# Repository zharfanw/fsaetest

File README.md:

# UII's FSAE Car TEST

<!--stackedit_data:
eyJoaXN0b3J5IjpbNDYwMDQ0OTMzXX0=
-->

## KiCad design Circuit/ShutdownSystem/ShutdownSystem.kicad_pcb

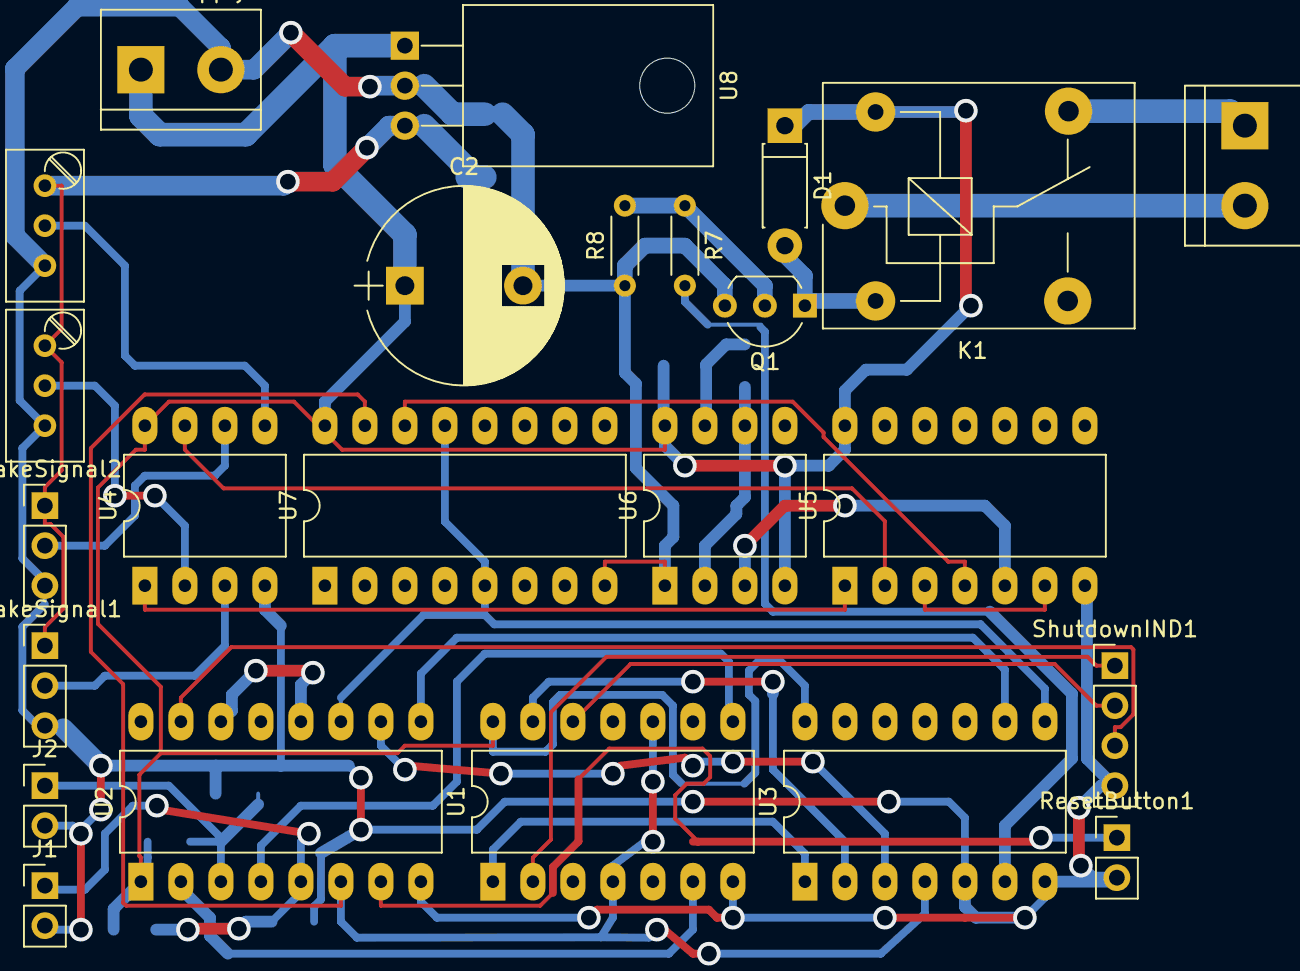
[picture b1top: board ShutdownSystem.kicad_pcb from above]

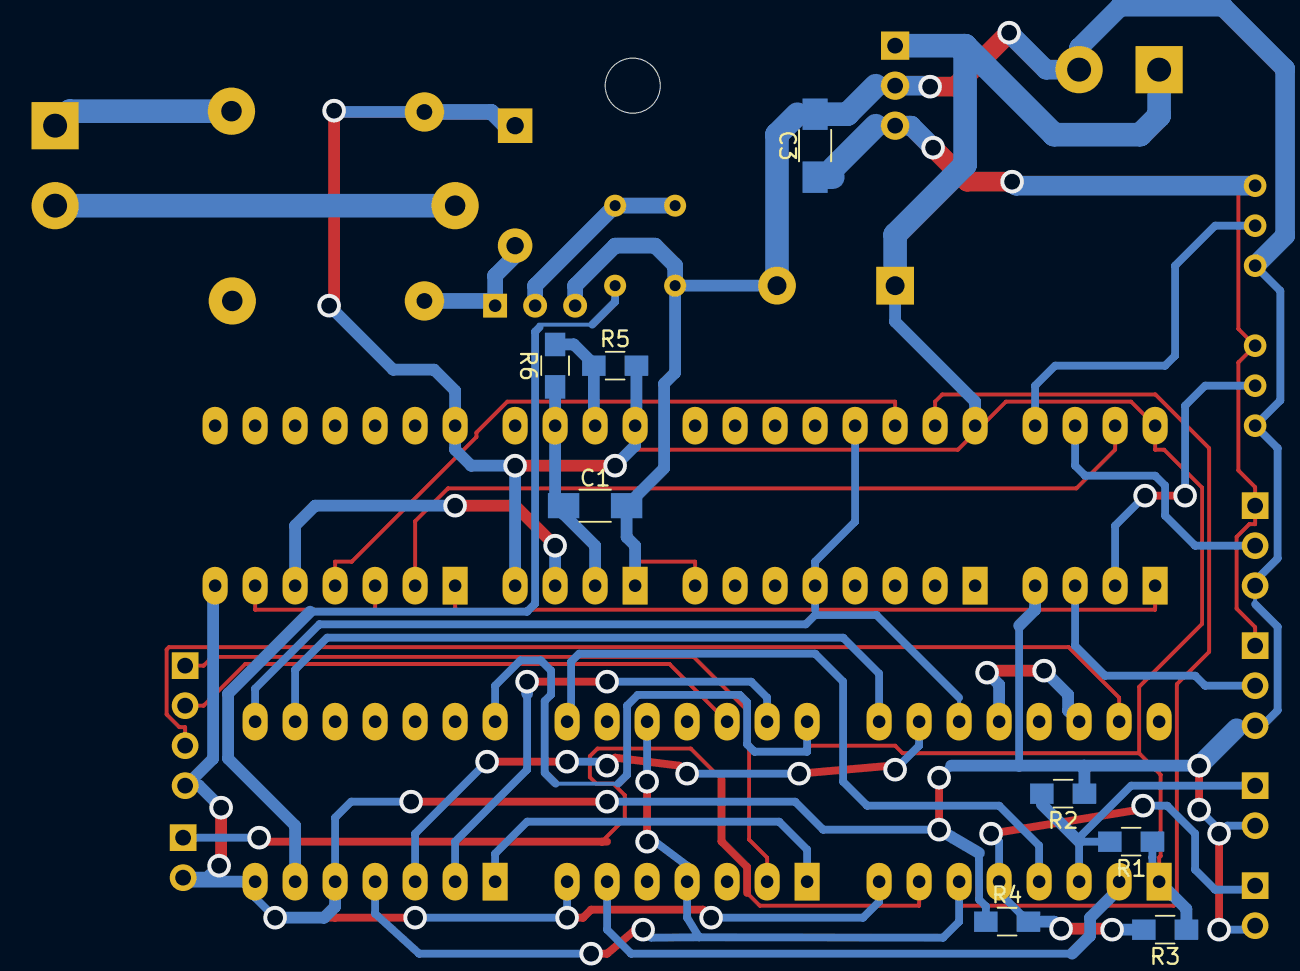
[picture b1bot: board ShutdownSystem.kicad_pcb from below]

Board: 2 copper layers, 32 parts (8 on the bottom side), 34 nets.

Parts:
BrakeSignal1, BrakeSignal2: XH_3p; Pin_Header_Straight_1x03_Pitch2.54mm
C1: 4u7F; C_1206_HandSoldering
C2: 100uF; CP_Radial_D12.5mm_P7.50mm
C3: 10uF; C_1206_HandSoldering
D1: D; D_DO-41_SOD81_P7.62mm_Horizontal
J1, J2: Conn_01x02_Male; Pin_Header_Straight_1x02_Pitch2.54mm
K1: SANYOU_SRD_Form_C; Relay_SPDT_SANYOU_SRD_Series_Form_C
PowerSupply1: TerminalBlock_2p; TerminalBlock_bornier-2_P5.08mm
Q1: 2N3906; TO-92_Inline_Wide
R1, R2, R3, R4: R; R_0805_HandSoldering
R5: 3k; R_0805_HandSoldering
R6: 13k; R_0805_HandSoldering
R7, R8: R; R_Axial_DIN0204_L3.6mm_D1.6mm_P5.08mm_Horizontal
RV1, RV2: 10k; Potentiometer_Trimmer_Bourns_3296W
ResetButton1: Xh_2p; Pin_Header_Straight_1x02_Pitch2.54mm
ShutdownCircuit1: TerminalBlock_2p; TerminalBlock_bornier-2_P5.08mm
ShutdownIND1: Conn_01x04; Pin_Header_Straight_1x04_Pitch2.54mm
U1: 4013; DIP-14_W10.16mm_LongPads
U2: 4049; DIP-16_W10.16mm_LongPads
U3: 4025; DIP-14_W10.16mm_LongPads
U4: TL072; DIP-8_W10.16mm_LongPads
U5: 4081; DIP-14_W10.16mm_LongPads
U6: NE555; DIP-8_W10.16mm_LongPads
U7: 4017; DIP-16_W10.16mm_LongPads
U8: L7805; TO-220-3_Horizontal

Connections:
+5V: BrakeSignal1.1, BrakeSignal2.1, C3.1, RV1.1, RV2.1, U8.3
/BMS_IND: ShutdownIND1.1, U1.2
/BMS_Status: J2.1, R1.2, R2.2, U2.3
/BSPD_Status: U2.11, U3.8, U7.5, U7.13
/Clock: U5.5, U6.3
/IMD_IND: ShutdownIND1.2, U1.12
/IMD_Status: J1.1, R3.2, R4.2, U2.5
/Reset: ResetButton1.1, U2.7
/Shutdown_IN: K1.4, ShutdownCircuit1.1
/Shutdown_OUT: K1.1, ShutdownCircuit1.2
GND: BrakeSignal1.3, BrakeSignal2.3, C1.2, C2.2, C3.2, J1.2, J2.2, PowerSupply1.2, Q1.3, R2.1, R4.1, R8.1, RV1.3, RV2.3, ResetButton1.2, ShutdownIND1.4, U1.7, U2.8, U3.5, U3.7, U4.4, U5.7, U6.1, U7.8, U8.2
unnamed: BrakeSignal1.2, U4.3
unnamed: BrakeSignal2.2, U4.6
unnamed: C1.1, R6.1, U6.2, U6.6
unnamed: D1.2, K1.2, Q1.1
unnamed: Q1.2, R7.1, R8.2
unnamed: R5.1, R6.2, U6.7
unnamed: R7.2, U3.6
unnamed: RV1.2, U4.2
unnamed: RV2.2, U4.5
unnamed: ShutdownIND1.3, U2.15
unnamed: U1.1, U3.1
unnamed: U1.6, U2.2
unnamed: U1.8, U2.4
unnamed: U1.4, U1.10, U2.6, U3.4, U7.15
unnamed: U1.13, U3.2
unnamed: U2.9, U3.9
unnamed: U2.10, U3.3
unnamed: U2.12, U2.14
unnamed: U4.1, U5.1
unnamed: U4.7, U5.2
unnamed: U5.3, U5.6
unnamed: U5.4, U7.14
VCC: C2.1, D1.1, K1.5, PowerSupply1.1, R1.1, R3.1, R5.2, U1.14, U2.1, U3.14, U4.8, U5.14, U6.4, U6.8, U7.16, U8.1

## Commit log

2019-12-07 New Added
2019-12-07 README.md updated from https://stackedit.io/
